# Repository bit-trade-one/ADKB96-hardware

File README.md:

# ADKB96

## [The production method manual is here! ](http://bit-trade-one.co.jp/selfmadekb/adkb96manual/) (Sorry, now japanese only ...)

### [Firmware writing procedure (external site)](https://bit-trade-one.co.jp/selfmadekb/softwaremanual/)

## Standard 96 key type base model.

It is a standard rectangle (rectangular) base model of vertical 6 x horizontal 16 keys.
Recommended for those who want to make it first, and those who want to stick to the type of key in orthodox form.
Comfortable to use as a tester with various switches and key tops.

## Compact and easy to carry. Also supports tilt.

The compact acrylic case with a thickness of 20 mm is easy to handle and matches various desks.
Use of the tilt is also possible by using the included stand.

## please note!

To use this product, you need a general knowledge of electronic work and electronic circuits. Also, key tops and key switches are not included.
Please prepare your own by yourself.

### <Product specification>

- Supported interface: USB MicroB
- Maximum number of keys: 96
- Supported key switch: Cherry MX / Kailh Low Profile
- Body size 310 x D 115 x H 20 mm
- Weight: about 300g ※ The dimensions and weight are measured with the kit only
- Operating environment: Temperature: 0 to 45 ° C, humidity 10 to 60% (thing without condensation)
- Contents: complete set / parts list & preparation manual guide 1 part / kit repair guide 1 part
- Producing country: Made in Japan
- Warranty period: Only initial failure of parts is supported. Operation after assembly is not covered by warranty.

| Part name | Quantity |
|:-: |:-: |
| * Pro Micro compatible products (firmware has been written) | 2 |
| Diode 1N4148 (THD) | 96 |
| Tact switch | 2 |
| * Micro USB Cable | 1 |
| Spacer | 14 |
| Screw | 28 |
| Cushion rubber seal | 8 |
| Round washer | 4 |
| Substrate | 1 |
| Acrylic set | 1 |

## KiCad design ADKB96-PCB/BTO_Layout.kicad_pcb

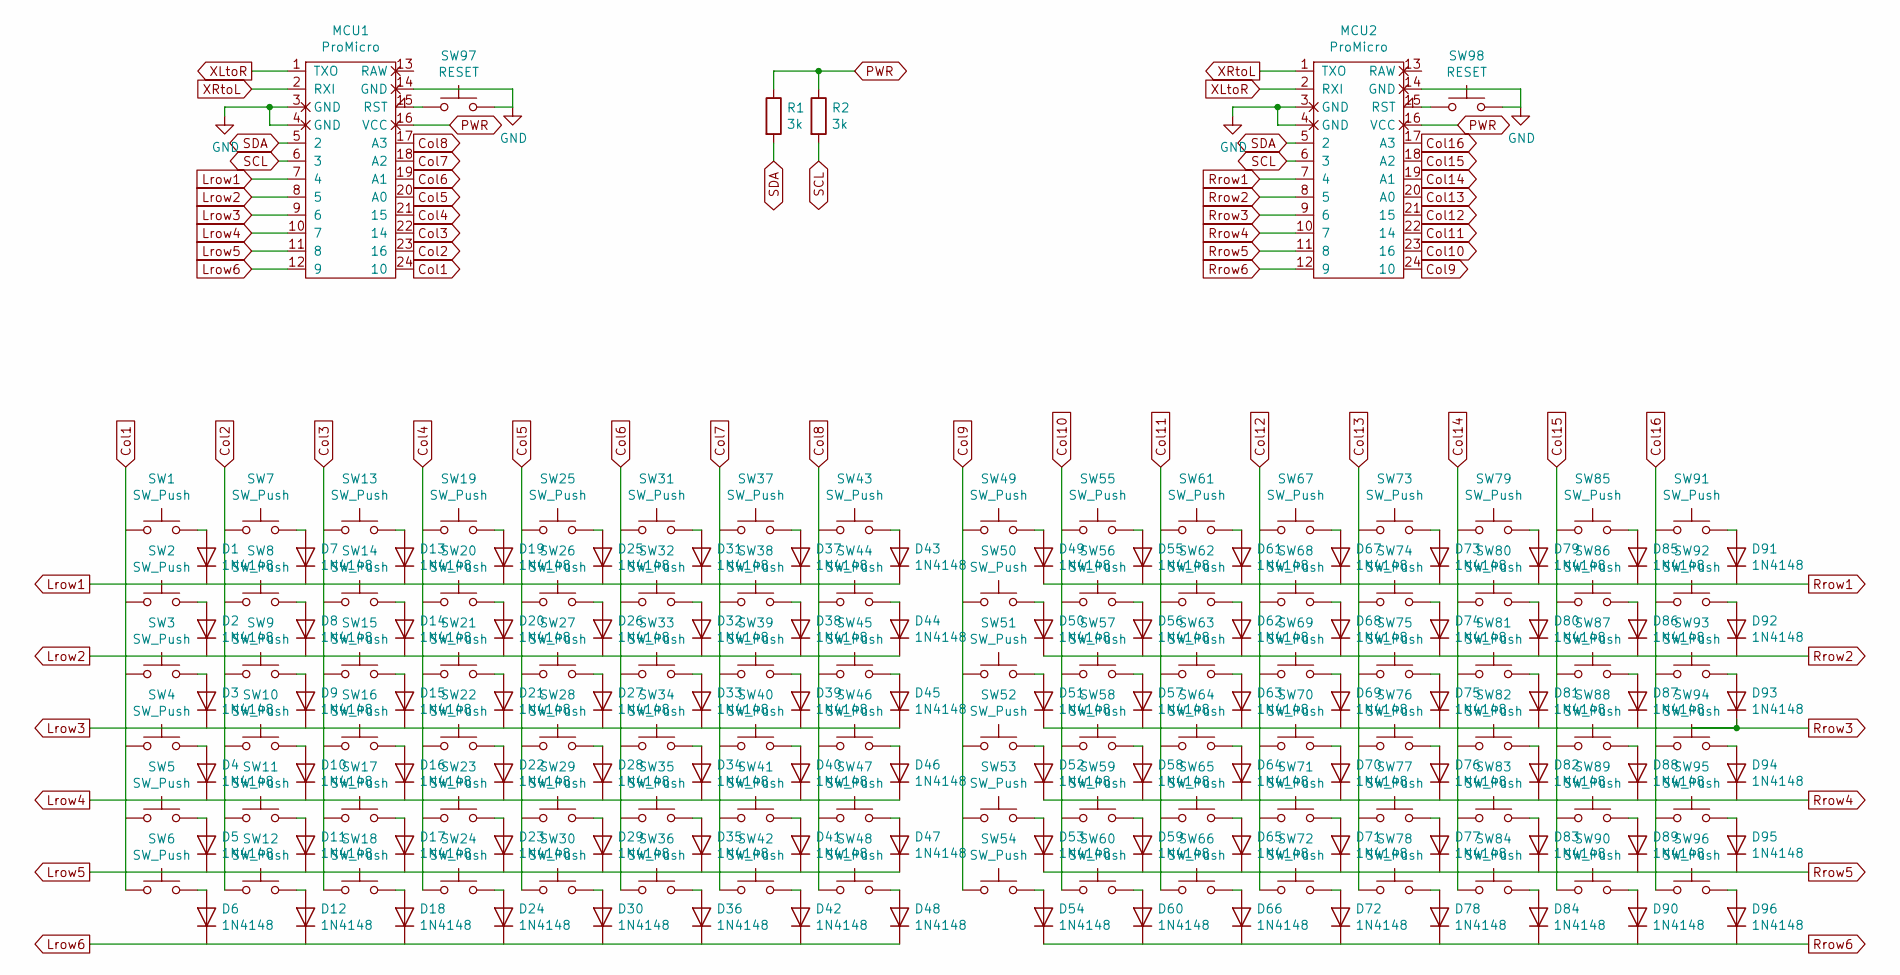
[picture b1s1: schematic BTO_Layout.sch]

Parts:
D1, D2, D3, D4, D5, D6, D7, D8, D9, D10, D11, D12, D13, D14, D15, D16, D17, D18, D19, D20, D21, D22, D23, D24, D25, D26, D27, D28, D29, D30, D31, D32, D33, D34, D35, D36, D37, D38, D39, D40, D41, D42, D43, D44, D45, D46, D47, D48, D49, D50, D51, D52, D53, D54, D55, D56, D57, D58, D59, D60, D61, D62, D63, D64, D65, D66, D67, D68, D69, D70, D71, D72, D73, D74, D75, D76, D77, D78, D79, D80, D81, D82, D83, D84, D85, D86, D87, D88, D89, D90, D91, D92, D93, D94, D95, D96: 1N4148; Diode_Keyboard_10_16
MCU1, MCU2: ProMicro; Pro_Micro
R1, R2: 3k; R_Axial_DIN0207_L6.3mm_D2.5mm_P10.16mm_Horizontal
SW1, SW2, SW3, SW4, SW5, SW6, SW7, SW8, SW9, SW10, SW11, SW12, SW13, SW14, SW15, SW16, SW17, SW18, SW19, SW20, SW21, SW22, SW23, SW24, SW25, SW26, SW27, SW28, SW29, SW30, SW31, SW32, SW33, SW34, SW35, SW36, SW37, SW38, SW39, SW40, SW41, SW42, SW43, SW44, SW45, SW46, SW47, SW48, SW49, SW50, SW51, SW52, SW53, SW54, SW55, SW56, SW57, SW58, SW59, SW60, SW61, SW62, SW63, SW64, SW65, SW66, SW67, SW68, SW69, SW70, SW71, SW72, SW73, SW74, SW75, SW76, SW77, SW78, SW79, SW80, SW81, SW82, SW83, SW84, SW85, SW86, SW87, SW88, SW89, SW90, SW91, SW92, SW93, SW94, SW95, SW96: SW_Push; SW_Cherry_Kailh_ALPS
SW97, SW98: RESET; SW_PUSH_6mm

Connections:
Col1: MCU1.24 (10), SW1.1, SW2.1, SW3.1, SW4.1, SW5.1, SW6.1
Col2: MCU1.23 (16), SW7.1, SW8.1, SW9.1, SW10.1, SW11.1, SW12.1
Col3: MCU1.22 (14), SW13.1, SW14.1, SW15.1, SW16.1, SW17.1, SW18.1
Col4: MCU1.21 (15), SW19.1, SW20.1, SW21.1, SW22.1, SW23.1, SW24.1
Col5: MCU1.20 (A0), SW25.1, SW26.1, SW27.1, SW28.1, SW29.1, SW30.1
Col6: MCU1.19 (A1), SW31.1, SW32.1, SW33.1, SW34.1, SW35.1, SW36.1
Col7: MCU1.18 (A2), SW37.1, SW38.1, SW39.1, SW40.1, SW41.1, SW42.1
Col8: MCU1.17 (A3), SW43.1, SW44.1, SW45.1, SW46.1, SW47.1, SW48.1
Col9: MCU2.24 (10), SW49.1, SW50.1, SW51.1, SW52.1, SW53.1, SW54.1
Col10: MCU2.23 (16), SW55.1, SW56.1, SW57.1, SW58.1, SW59.1, SW60.1
Col11: MCU2.22 (14), SW61.1, SW62.1, SW63.1, SW64.1, SW65.1, SW66.1
Col12: MCU2.21 (15), SW67.1, SW68.1, SW69.1, SW70.1, SW71.1, SW72.1
Col13: MCU2.20 (A0), SW73.1, SW74.1, SW75.1, SW76.1, SW77.1, SW78.1
Col14: MCU2.19 (A1), SW79.1, SW80.1, SW81.1, SW82.1, SW83.1, SW84.1
Col15: MCU2.18 (A2), SW85.1, SW86.1, SW87.1, SW88.1, SW89.1, SW90.1
Col16: MCU2.17 (A3), SW91.1, SW92.1, SW93.1, SW94.1, SW95.1, SW96.1
GND: MCU1.3 (GND), MCU1.4 (GND), MCU1.14 (GND), MCU2.3 (GND), MCU2.4 (GND), MCU2.14 (GND), SW97.2, SW98.2
Lrow1: D1.1 (K), D7.1 (K), D13.1 (K), D19.1 (K), D25.1 (K), D31.1 (K), D37.1 (K), D43.1 (K), MCU1.7 (4)
Lrow2: D2.1 (K), D8.1 (K), D14.1 (K), D20.1 (K), D26.1 (K), D32.1 (K), D38.1 (K), D44.1 (K), MCU1.8 (5)
Lrow3: D3.1 (K), D9.1 (K), D15.1 (K), D21.1 (K), D27.1 (K), D33.1 (K), D39.1 (K), D45.1 (K), MCU1.9 (6)
Lrow4: D4.1 (K), D10.1 (K), D16.1 (K), D22.1 (K), D28.1 (K), D34.1 (K), D40.1 (K), D46.1 (K), MCU1.10 (7)
Lrow5: D5.1 (K), D11.1 (K), D17.1 (K), D23.1 (K), D29.1 (K), D35.1 (K), D41.1 (K), D47.1 (K), MCU1.11 (8)
Lrow6: D6.1 (K), D12.1 (K), D18.1 (K), D24.1 (K), D30.1 (K), D36.1 (K), D42.1 (K), D48.1 (K), MCU1.12 (9)
unnamed: D1.2 (A), SW1.2
unnamed: D2.2 (A), SW2.2
unnamed: D3.2 (A), SW3.2
unnamed: D4.2 (A), SW4.2
unnamed: D5.2 (A), SW5.2
unnamed: D6.2 (A), SW6.2
unnamed: D7.2 (A), SW7.2
unnamed: D8.2 (A), SW8.2
unnamed: D9.2 (A), SW9.2
unnamed: D10.2 (A), SW10.2
unnamed: D11.2 (A), SW11.2
unnamed: D12.2 (A), SW12.2
unnamed: D13.2 (A), SW13.2
unnamed: D14.2 (A), SW14.2
unnamed: D15.2 (A), SW15.2
unnamed: D16.2 (A), SW16.2
unnamed: D17.2 (A), SW17.2
unnamed: D18.2 (A), SW18.2
unnamed: D19.2 (A), SW19.2
unnamed: D20.2 (A), SW20.2
unnamed: D21.2 (A), SW21.2
unnamed: D22.2 (A), SW22.2
unnamed: D23.2 (A), SW23.2
unnamed: D24.2 (A), SW24.2
unnamed: D25.2 (A), SW25.2
unnamed: D26.2 (A), SW26.2
unnamed: D27.2 (A), SW27.2
unnamed: D28.2 (A), SW28.2
unnamed: D29.2 (A), SW29.2
unnamed: D30.2 (A), SW30.2
unnamed: D31.2 (A), SW31.2
unnamed: D32.2 (A), SW32.2
unnamed: D33.2 (A), SW33.2
unnamed: D34.2 (A), SW34.2
unnamed: D35.2 (A), SW35.2
unnamed: D36.2 (A), SW36.2
unnamed: D37.2 (A), SW37.2
unnamed: D38.2 (A), SW38.2
unnamed: D39.2 (A), SW39.2
unnamed: D40.2 (A), SW40.2
unnamed: D41.2 (A), SW41.2
unnamed: D42.2 (A), SW42.2
unnamed: D43.2 (A), SW43.2
unnamed: D44.2 (A), SW44.2
unnamed: D45.2 (A), SW45.2
unnamed: D46.2 (A), SW46.2
unnamed: D47.2 (A), SW47.2
unnamed: D48.2 (A), SW48.2
unnamed: D49.2 (A), SW49.2
unnamed: D50.2 (A), SW50.2
unnamed: D51.2 (A), SW51.2
unnamed: D52.2 (A), SW52.2
unnamed: D53.2 (A), SW53.2
unnamed: D54.2 (A), SW54.2
unnamed: D55.2 (A), SW55.2
unnamed: D56.2 (A), SW56.2
unnamed: D57.2 (A), SW57.2
unnamed: D58.2 (A), SW58.2
unnamed: D59.2 (A), SW59.2
unnamed: D60.2 (A), SW60.2
unnamed: D61.2 (A), SW61.2
unnamed: D62.2 (A), SW62.2
unnamed: D63.2 (A), SW63.2
unnamed: D64.2 (A), SW64.2
unnamed: D65.2 (A), SW65.2
unnamed: D66.2 (A), SW66.2
unnamed: D67.2 (A), SW67.2
unnamed: D68.2 (A), SW68.2
unnamed: D69.2 (A), SW69.2
unnamed: D70.2 (A), SW70.2
unnamed: D71.2 (A), SW71.2
unnamed: D72.2 (A), SW72.2
unnamed: D73.2 (A), SW73.2
unnamed: D74.2 (A), SW74.2
unnamed: D75.2 (A), SW75.2
unnamed: D76.2 (A), SW76.2
unnamed: D77.2 (A), SW77.2
unnamed: D78.2 (A), SW78.2
unnamed: D79.2 (A), SW79.2
unnamed: D80.2 (A), SW80.2
unnamed: D81.2 (A), SW81.2
unnamed: D82.2 (A), SW82.2
unnamed: D83.2 (A), SW83.2
unnamed: D84.2 (A), SW84.2
unnamed: D85.2 (A), SW85.2
unnamed: D86.2 (A), SW86.2
unnamed: D87.2 (A), SW87.2
unnamed: D88.2 (A), SW88.2
unnamed: D89.2 (A), SW89.2
unnamed: D90.2 (A), SW90.2
unnamed: D91.2 (A), SW91.2
unnamed: D92.2 (A), SW92.2
unnamed: D93.2 (A), SW93.2
unnamed: D94.2 (A), SW94.2
unnamed: D95.2 (A), SW95.2
unnamed: D96.2 (A), SW96.2
unnamed: MCU1.15 (RST), SW97.1
unnamed: MCU2.15 (RST), SW98.1
PWR: MCU1.16 (VCC), MCU2.16 (VCC), R1.1, R2.1
Rrow1: D49.1 (K), D55.1 (K), D61.1 (K), D67.1 (K), D73.1 (K), D79.1 (K), D85.1 (K), D91.1 (K), MCU2.7 (4)
Rrow2: D50.1 (K), D56.1 (K), D62.1 (K), D68.1 (K), D74.1 (K), D80.1 (K), D86.1 (K), D92.1 (K), MCU2.8 (5)
Rrow3: D51.1 (K), D57.1 (K), D63.1 (K), D69.1 (K), D75.1 (K), D81.1 (K), D87.1 (K), D93.1 (K), MCU2.9 (6)
Rrow4: D52.1 (K), D58.1 (K), D64.1 (K), D70.1 (K), D76.1 (K), D82.1 (K), D88.1 (K), D94.1 (K), MCU2.10 (7)
Rrow5: D53.1 (K), D59.1 (K), D65.1 (K), D71.1 (K), D77.1 (K), D83.1 (K), D89.1 (K), D95.1 (K), MCU2.11 (8)
Rrow6: D54.1 (K), D60.1 (K), D66.1 (K), D72.1 (K), D78.1 (K), D84.1 (K), D90.1 (K), D96.1 (K), MCU2.12 (9)
SCL: MCU1.6 (3), MCU2.6 (3), R2.2
SDA: MCU1.5 (2), MCU2.5 (2), R1.2
XLtoR: MCU1.1 (TXO), MCU2.2 (RXI)
XRtoL: MCU1.2 (RXI), MCU2.1 (TXO)

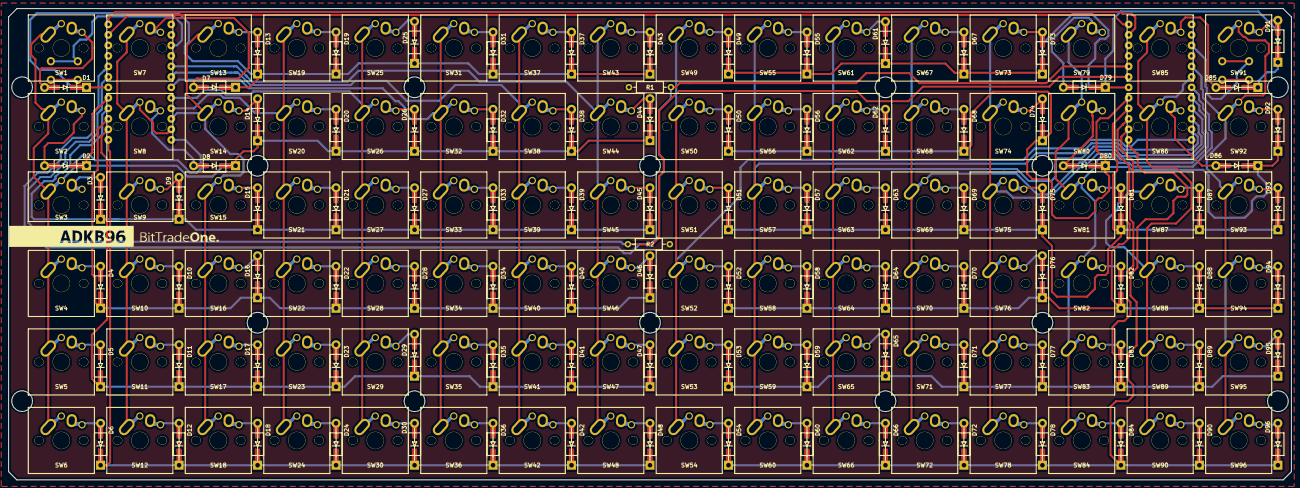
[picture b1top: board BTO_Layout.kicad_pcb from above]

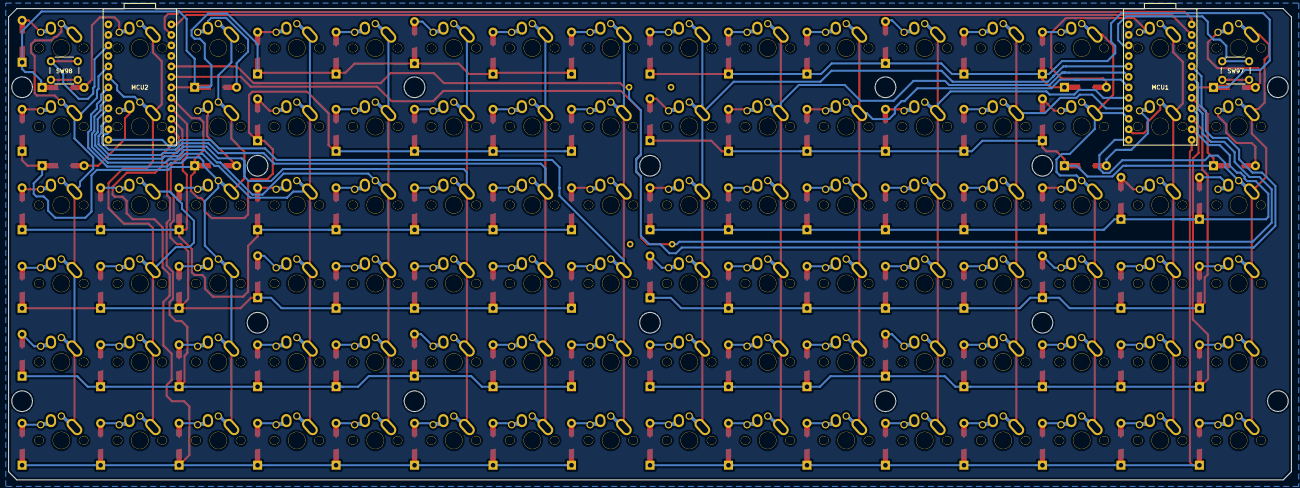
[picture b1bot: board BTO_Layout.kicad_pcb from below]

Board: 2 copper layers, 310.6 x 114.1 mm, 198 parts (2 on the bottom side), 132 nets.

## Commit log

2021-12-01 Update README.md
    画像追加
